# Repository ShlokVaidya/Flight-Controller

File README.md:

# Single Flight Controller (SFC) – Project Documentation

This repository contains the design files, schematic, and explanation for my custom Single Flight Controller (SFC). The goal of this project was to create a compact, modular, and fully functional flight controller with built-in sensors, logging capability, and support for standard RC aircraft peripherals. This design was heavily inspired by Hack Club’s Guided Project: SFC.

## Overview

This flight controller integrates all the essential modules required for basic autonomous flight experimentation on a single PCB. It includes computation, sensing, logging, and connectivity features normally spread across multiple boards.

The system is built around an STM32 microcontroller, with supporting components for power regulation, sensor interfacing, GPS reception, and servo control.

---

## Features

### 1. Microcontroller

The design centers around an STM32F722RETx MCU. It provides high-speed processing, multiple UART/SPI/I2C peripherals, and enough GPIO pins for sensors and servo output.

### 2. Four 3-Pin Servo Connectors

The board includes four standard 3-pin (Signal, 5V, GND) servo output connectors.
These can be used for:

* Control surfaces (aileron, elevator, rudder)
* Throttle signal
* Or any PWM-output peripheral

The PCB includes appropriate decoupling capacitors and routing to ensure clean, low-noise PWM signals.

### 3. UART Port

A dedicated UART port is broken out on the PCB.
This can be used for:

* Telemetry modules
* Debug serial output
* External communication
* RC Receiver (if using SBUS or another serial protocol)

### 4. Built-In Sensors and Modules

#### GPS Module: u-blox Neo-M9N

A high-performance GNSS receiver is integrated directly onto the PCB.
Features include:

* Fast acquisition
* High update rate options
* Reliable lock in outdoor flight conditions
* Direct UART communication with the STM32

#### Barometer

The barometer module (BMP-series) provides altitude estimation for stability and navigation algorithms.
It interfaces over I2C and includes proper filtering capacitors for noise reduction.

#### Accelerometer and Temperature Sensor

An onboard IMU provides acceleration data for movement detection and flight stabilization.
Temperature reading is also used internally by IMUs to compensate sensor drift.

### 5. SD Card Slot for Data Logging

The board includes a microSD card slot for logging flight data such as:

* GPS coordinates
* Barometric altitude
* Acceleration
* Temperature
* System debug information

The microcontroller communicates with the SD card via SPI.

### 6. Power Management

The design includes onboard regulators and filtering stages to provide stable supplies for:

* 5V rail (servos and peripherals)
* 3.3V rail (MCU, sensors, GPS)
* Noise isolation between digital and analog sections

---

## How the Flight Controller Was Designed

### Schematic Stage

I began by identifying the essential modules needed for the first version of the flight controller. I collected reference designs from datasheets and existing open-source boards, then arranged everything into a master schematic. Each module was divided into blocks:

* MCU core section
* Power regulation
* Servo outputs
* GPS
* Sensors (Barometer + IMU)
* SD card interface
* UART and additional connectors

I ensured all power, ground, and communication lines were properly labeled and referenced across schematic pages.

### PCB Routing

This was the most challenging part of the entire project.

#### Challenges Faced

1. **Dense routing around the STM32F7 MCU**
   The microcontroller has many high-speed pins in tight clusters. Routing SPI, I2C, UART, SWD, and PWM signals without crossing too many traces was difficult.

2. **Interference concerns between GPS and digital signals**
   GPS modules are sensitive to noise. Keeping the antenna section clean required careful placement and ground-plane management.

3. **Power distribution**
   Servos can draw significant current. Ensuring thick enough traces and minimizing voltage drops was a challenge.

4. **SD Card signal integrity**
   SPI lines need clean routing and matched lengths to avoid read/write instability. I had to reroute multiple times to avoid crosstalk.

5. **Fitting everything on a reasonable board size**
   With multiple connectors, sensors, and the MCU, arranging components efficiently took several iterations.

### What I Learned

1. **Importance of reference designs**
   Studying vendor schematics helped avoid basic mistakes, especially with decoupling and pull-up requirements.

2. **Routing strategy matters**
   Planning major traces (power rails, GPS lines, SD card lines) before others saves time.

3. **Decoupling capacitors are not optional**
   Correct placement greatly affected reliability during testing.

4. **Grounding techniques for mixed-signal boards**
   Separating analog and digital grounds and using ground pours improved noise performance.

5. **Iterative design is normal**
   The first layout is rarely perfect. Revision cycles teach you more than documentation ever will.

---

## Reference

This project was inspired by and based on concepts from Hack Club’s Guided Project: Single Flight Controller (SFC).

Their documentation, examples, and approach helped me understand:

* How to break complex designs into modular blocks
* Good PCB routing practices
* How sensing modules interact on a flight controller
* The importance of logging and debugging tools

---

## Conclusion

This Single Flight Controller is the result of combining research, reference designs, and hands-on PCB design practice. With integrated GPS, IMU, barometer, servo outputs, UART, and SD card logging on one board, it serves as a compact platform for experimenting with flight algorithms and embedded systems.

Note: 
Due to unavaiable components on JLCPCB i would request to get tickets instead of the PCB.

Thank You,
Shlok Vaidya

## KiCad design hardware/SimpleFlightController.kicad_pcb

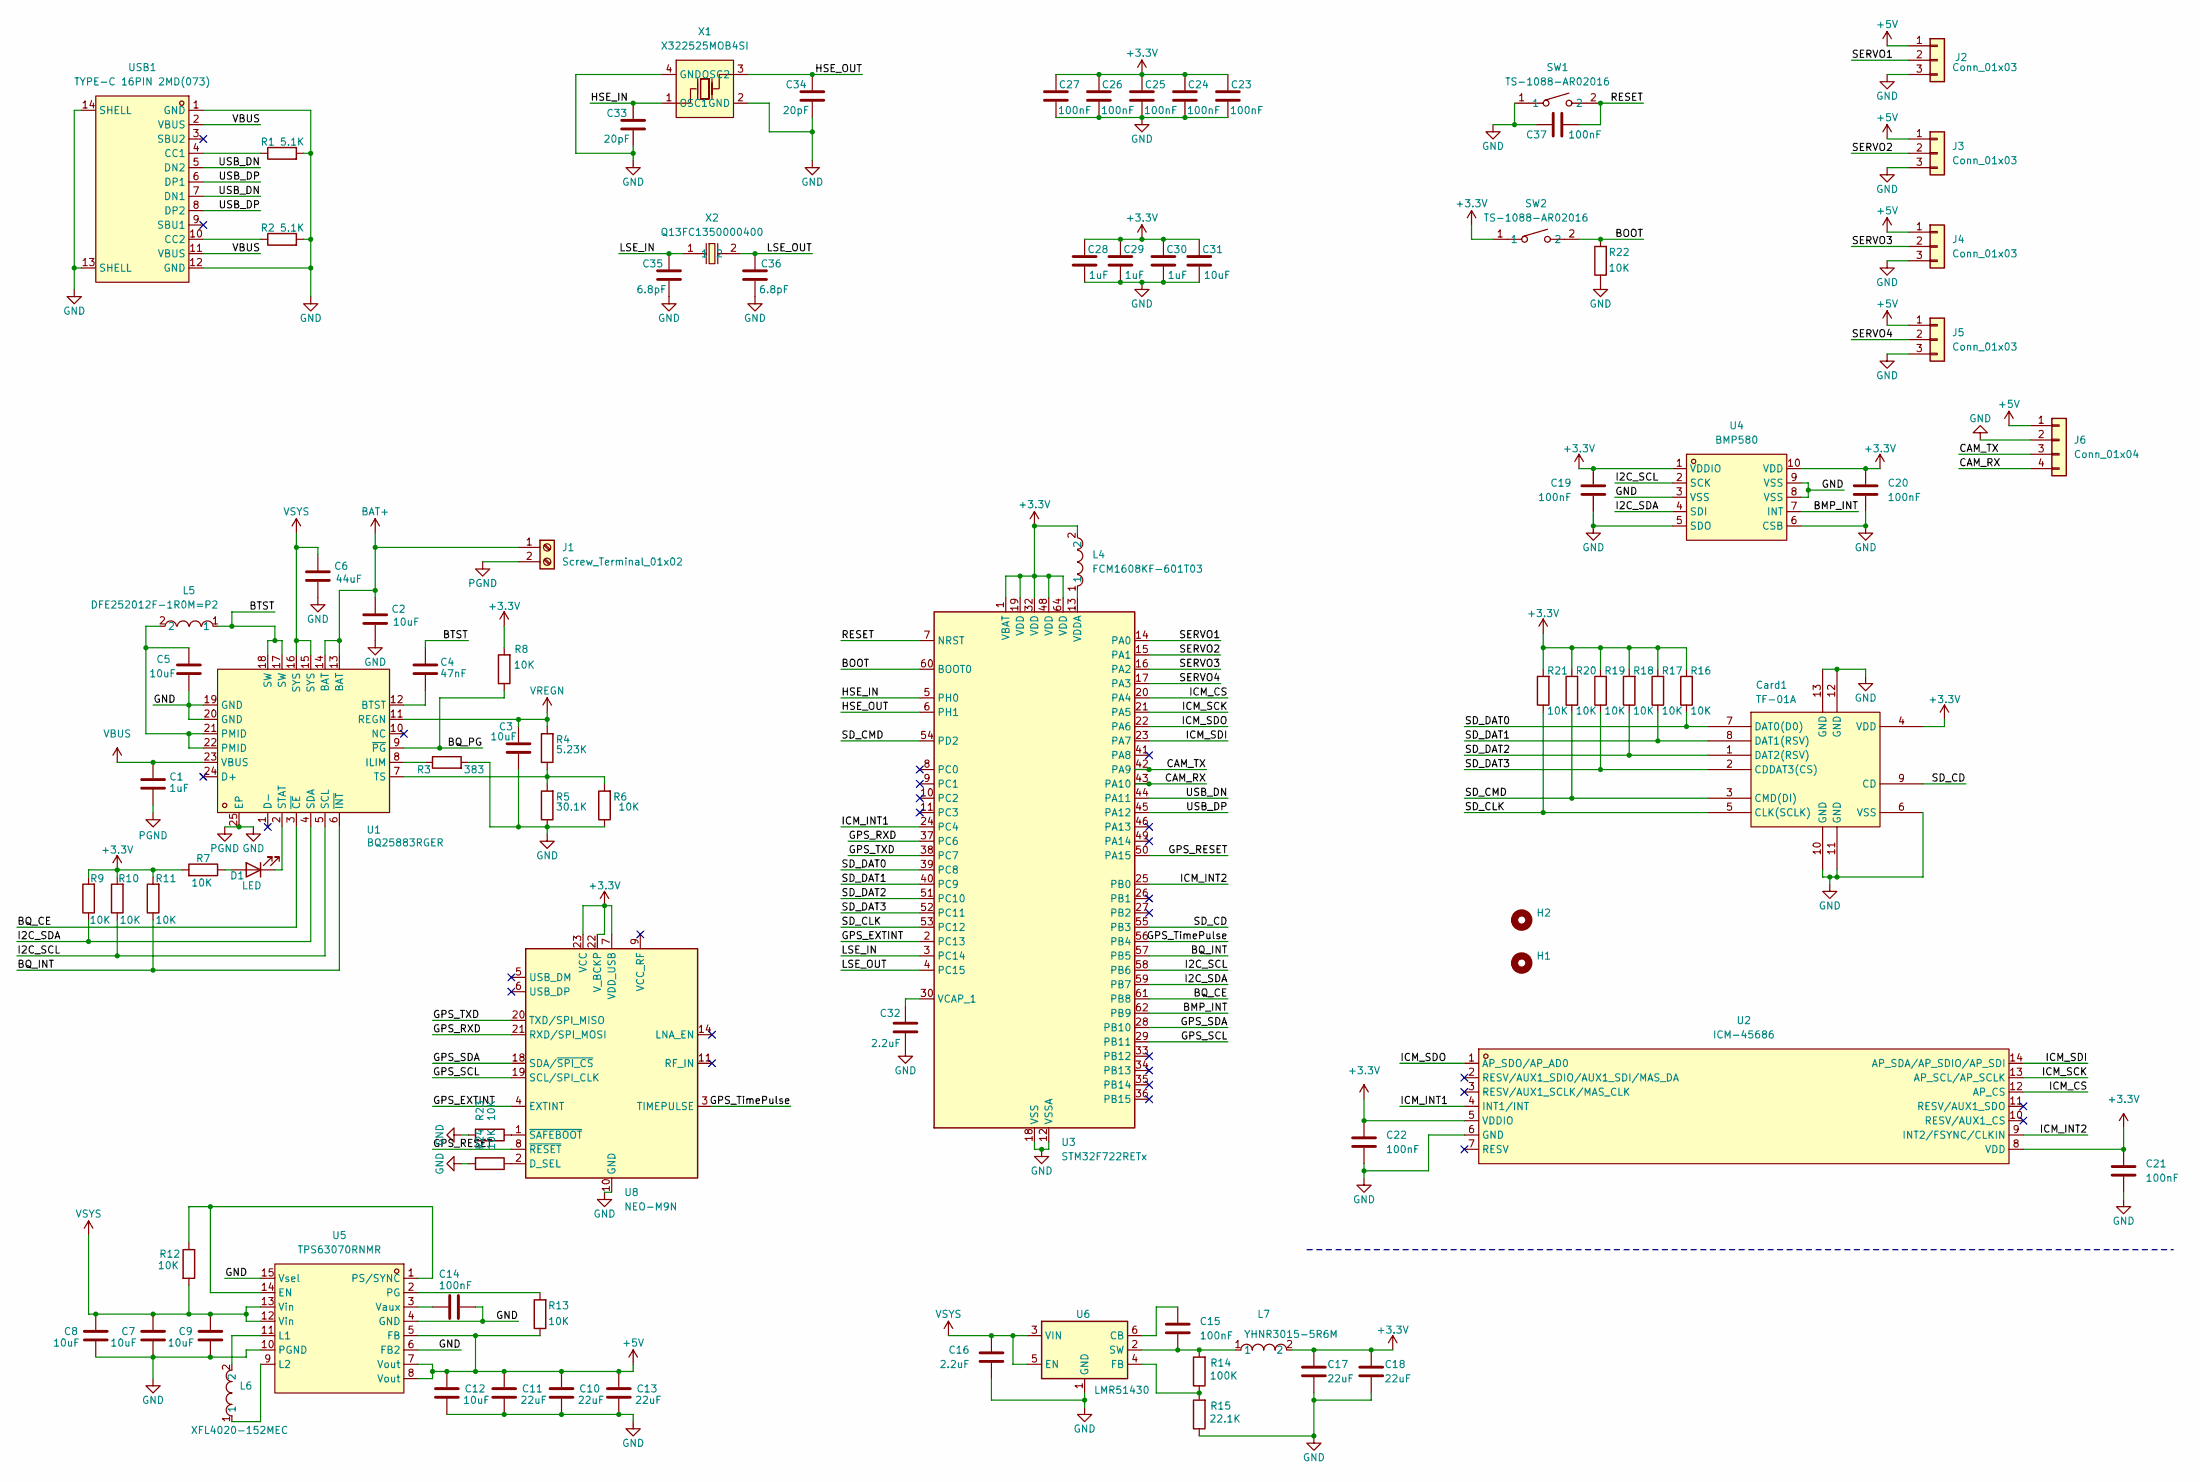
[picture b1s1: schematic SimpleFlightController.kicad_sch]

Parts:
C1, C28, C29, C30: 1uF; C_0402_1005Metric
C2, C9, C12: 10uF; C_0603_1608Metric
C3, C5, C31: 10uF; C_0402_1005Metric
C4: 47nF; C_0201_0603Metric
C6: 44uF; C_0603_1608Metric
C7, C8: 10uF; C_0805_2012Metric
C10, C11, C13: 22uF; C_0805_2012Metric
C14, C15, C19, C20, C21, C22, C23, C24, C25, C26, C27, C37: 100nF; C_0201_0603Metric
C16: 2.2uF; C_0603_1608Metric
C17, C18: 22uF; C_0402_1005Metric
C32: 2.2uF; C_0201_0603Metric
C33, C34: 20pF; C_0201_0603Metric
C35, C36: 6.8pF; C_0201_0603Metric
Card1: TF-01A; TF-SMD_TF-01A; LCSC Part C91145
D1: LED; LED_0402_1005Metric
H1, H2: MountingHole; MountingHole_2.2mm_M2
J1: Screw_Terminal_01x02; TerminalBlock_Xinya_XY308-2.54-2P_1x02_P2.54mm_Horizontal
J2, J3, J4, J5: Conn_01x03; PinHeader_1x03_P2.54mm_Vertical
J6: Conn_01x04; PinHeader_1x04_P2.54mm_Vertical
L4: FCM1608KF-601T03; L0603; LCSC Part C141723
L5: DFE252012F-1R0M=P2; L2520; LCSC Part C435392
L6: XFL4020-152MEC; IND-SMD_L4.0-W4.0-A; LCSC Part C3033018
L7: YHNR3015-5R6M; IND-SMD_L3.0-W3.0; LCSC Part C18236327
R1, R2: 5.1K; R_0201_0603Metric
R3: 383; R_0201_0603Metric
R4: 5.23K; R_0201_0603Metric
R5: 30.1K; R_0201_0603Metric
R6, R7, R8, R9, R10, R11, R12, R13, R16, R17, R18, R19, R20, R21, R22, R23, R24: 10K; R_0201_0603Metric
R14: 100K; R_0402_1005Metric
R15: 22.1K; R_0402_1005Metric
SW1, SW2: TS-1088-AR02016; SW-SMD_L3.9-W3.0-P4.45; LCSC Part C720477
U1: BQ25883RGER; VFQFPN-24_L4.0-W4.0-P0.50-BL-EP2.8; LCSC Part C544362
U2: ICM-45686; LGA-14_L3.0-W2.5-P0.50-TL; LCSC Part C22459454
U3: STM32F722RETx; LQFP-64_10x10mm_P0.5mm
U4: BMP580; LGA-10_L2.0-W2.0-P0.50-TL_BMP580; LCSC Part C22391138
U5: TPS63070RNMR; VQFN-HR-15_L3.0-W2.5-P0.50-BL_TPS63070RNMR; LCSC Part C109322
U6: LMR51430; SOT-23-6
U8: NEO-M9N; ublox_NEO
USB1: TYPE-C 16PIN 2MD(073); USB-C-SMD_TYPE-C-6PIN-2MD-073; LCSC Part C2765186
X1: X322525MOB4SI; CRYSTAL-SMD_4P-L3.2-W2.5-BL; LCSC Part C9006
X2: Q13FC1350000400; FC-135R_L3.2-W1.5; LCSC Part C32346

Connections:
+3.3V: C17.1, C18.1, C19.1, C20.1, C21.1, C22.1, C23.1, C24.1, C25.1, C26.1, C27.1, C28.1, C29.1, C30.1, C31.1, Card1.4 (VDD), L4.2, L7.2, R7.2, R8.2, R9.2, R10.2, R11.2, R16.2, R17.2, R18.2, R19.2, R20.2, R21.2, SW2.1, U2.5 (VDDIO), U2.8 (VDD), U3.1 (VBAT), U3.19 (VDD), U3.32 (VDD), U3.48 (VDD), U3.64 (VDD), U4.1 (VDDIO), U4.10 (VDD), U8.7 (VDD_USB), U8.22 (V_BCKP), U8.23 (VCC)
+5V: C10.1, C11.1, C12.1, C13.1, J2.1, J3.1, J4.1, J5.1, J6.1, R13.1, U5.5 (FB), U5.7 (Vout), U5.8 (Vout)
/BMP_INT: U3.62 (PB9), U4.7 (INT)
/BOOT: R22.2, SW2.2, U3.60 (BOOT0)
/BQ_CE: U1.3 (~CE), U3.61 (PB8)
/BQ_INT: R11.1, U1.6 (~INT), U3.57 (PB5)
/BQ_PG: R8.1, U1.9 (~PG)
/BTST: C4.1, L5.1, U1.17 (SW), U1.18 (SW)
/CAM_RX: J6.4, U3.43 (PA10)
/CAM_TX: J6.3, U3.42 (PA9)
/GPS_EXTINT: U3.2 (PC13), U8.4 (EXTINT)
/GPS_RESET: U3.50 (PA15), U8.8 (~RESET)
/GPS_RXD: U3.37 (PC6), U8.21 (RXD/SPI_MOSI)
/GPS_SCL: U3.29 (PB11), U8.19 (SCL/SPI_CLK)
/GPS_SDA: U3.28 (PB10), U8.18 (SDA/~SPI_CS)
/GPS_TXD: U3.38 (PC7), U8.20 (TXD/SPI_MISO)
/GPS_TimePulse: U3.56 (PB4), U8.3 (TIMEPULSE)
/HSE_IN: C33.1, U3.5 (PH0), X1.1 (OSC1)
/HSE_OUT: C34.1, U3.6 (PH1), X1.3 (OSC2)
/I2C_SCL: R10.1, U1.5 (SCL), U3.58 (PB6), U4.2 (SCK)
/I2C_SDA: R9.1, U1.4 (SDA), U3.59 (PB7), U4.4 (SDI)
/ICM_CS: U2.12 (AP_CS), U3.20 (PA4)
/ICM_INT1: U2.4 (INT1/INT), U3.24 (PC4)
/ICM_INT2: U2.9 (INT2/FSYNC/CLKIN), U3.25 (PB0)
/ICM_SCK: U2.13 (AP_SCL/AP_SCLK), U3.21 (PA5)
/ICM_SDI: U2.14 (AP_SDA/AP_SDIO/AP_SDI), U3.23 (PA7)
/ICM_SDO: U2.1 (AP_SDO/AP_AD0), U3.22 (PA6)
/LSE_IN: C35.1, U3.3 (PC14), X2.1
/LSE_OUT: C36.1, U3.4 (PC15), X2.2
/RESET: C37.2, SW1.2, U3.7 (NRST)
/SD_CD: Card1.9 (CD), U3.55 (PB3)
/SD_CLK: Card1.5 (CLK(SCLK)), R21.1, U3.53 (PC12)
/SD_CMD: Card1.3 (CMD(DI)), R20.1, U3.54 (PD2)
/SD_DAT0: Card1.7 (DAT0(D0)), R16.1, U3.39 (PC8)
/SD_DAT1: Card1.8 (DAT1(RSV)), R17.1, U3.40 (PC9)
/SD_DAT2: Card1.1 (DAT2(RSV)), R18.1, U3.51 (PC10)
/SD_DAT3: Card1.2 (CDDAT3(CS)), R19.1, U3.52 (PC11)
/SERVO1: J2.2, U3.14 (PA0)
/SERVO2: J3.2, U3.15 (PA1)
/SERVO3: J4.2, U3.16 (PA2)
/SERVO4: J5.2, U3.17 (PA3)
/USB_DN: U3.44 (PA11), USB1.5 (DN2), USB1.7 (DN1)
/USB_DP: U3.45 (PA12), USB1.6 (DP1), USB1.8 (DP2)
BAT+: C2.1, J1.1, U1.13 (BAT), U1.14 (BAT)
GND: C1.2, C2.2, C3.2, C5.2, C6.2, C7.2, C8.2, C9.2, C10.2, C11.2, C12.2, C13.2, C14.2, C16.2, C17.2, C18.2, C19.2, C20.2, C21.2, C22.2, C23.2, C24.2, C25.2, C26.2, C27.2, C28.2, C29.2, C30.2, C31.2, C32.2, C33.2, C34.2, C35.2, C36.2, C37.1, Card1.6 (VSS), Card1.10 (GND), Card1.11 (GND), Card1.12 (GND), Card1.13 (GND), J1.2, J2.3, J3.3, J4.3, J5.3, J6.2, R1.2, R2.2, R3.2, R5.1, R6.1, R15.1, R22.1, R23.2, R24.2, SW1.1, U1.19 (GND), U1.20 (GND), U1.25 (EP), U2.6 (GND), U3.12 (VSSA), U3.18 (VSS), U3.31 (VSS), U3.47 (VSS), U3.63 (VSS), U4.3 (VSS), U4.5 (SDO), U4.6 (CSB), U4.8 (VSS), U4.9 (VSS), U5.4 (GND), U5.6 (FB2), U5.10 (PGND), U5.15 (Vsel), U6.1 (GND), U8.10 (GND), U8.12 (GND), U8.13 (GND), U8.24 (GND), USB1.1 (GND), USB1.12 (GND), USB1.13 (SHELL), USB1.14 (SHELL), X1.2 (GND), X1.4 (GND)
unnamed: C5.1, L5.2, U1.21 (PMID), U1.22 (PMID)
unnamed: D1.2 (A), R7.1
unnamed: D1.1 (K), U1.2 (STAT)
unnamed: C4.2, U1.12 (BTST)
unnamed: R3.1, U1.8 (ILIM)
unnamed: R4.1, R5.2, R6.2, U1.7 (TS)
unnamed: C32.1, U3.30 (VCAP_1)
unnamed: L4.1, U3.13 (VDDA)
unnamed: R12.1, U5.1 (PS/SYNC), U5.14 (EN)
unnamed: L6.2, U5.11 (L1)
unnamed: L6.1, U5.9 (L2)
unnamed: R13.2, U5.2 (PG)
unnamed: C14.1, U5.3 (Vaux)
unnamed: C15.1, U6.6 (CB)
unnamed: R14.1, R15.2, U6.4 (FB)
unnamed: C15.2, L7.1, R14.2, U6.2 (SW)
unnamed: R24.1, U8.2 (D_SEL)
unnamed: R23.1, U8.1 (~SAFEBOOT)
unnamed: R1.1, USB1.4 (CC1)
unnamed: R2.1, USB1.10 (CC2)
VBUS: C1.1, U1.23 (VBUS), USB1.2 (VBUS), USB1.11 (VBUS)
VREGN: C3.1, R4.2, U1.11 (REGN)
VSYS: C6.1, C7.1, C8.1, C9.1, C16.1, R12.2, U1.15 (SYS), U1.16 (SYS), U5.12 (Vin), U5.13 (Vin), U6.3 (VIN), U6.5 (EN)

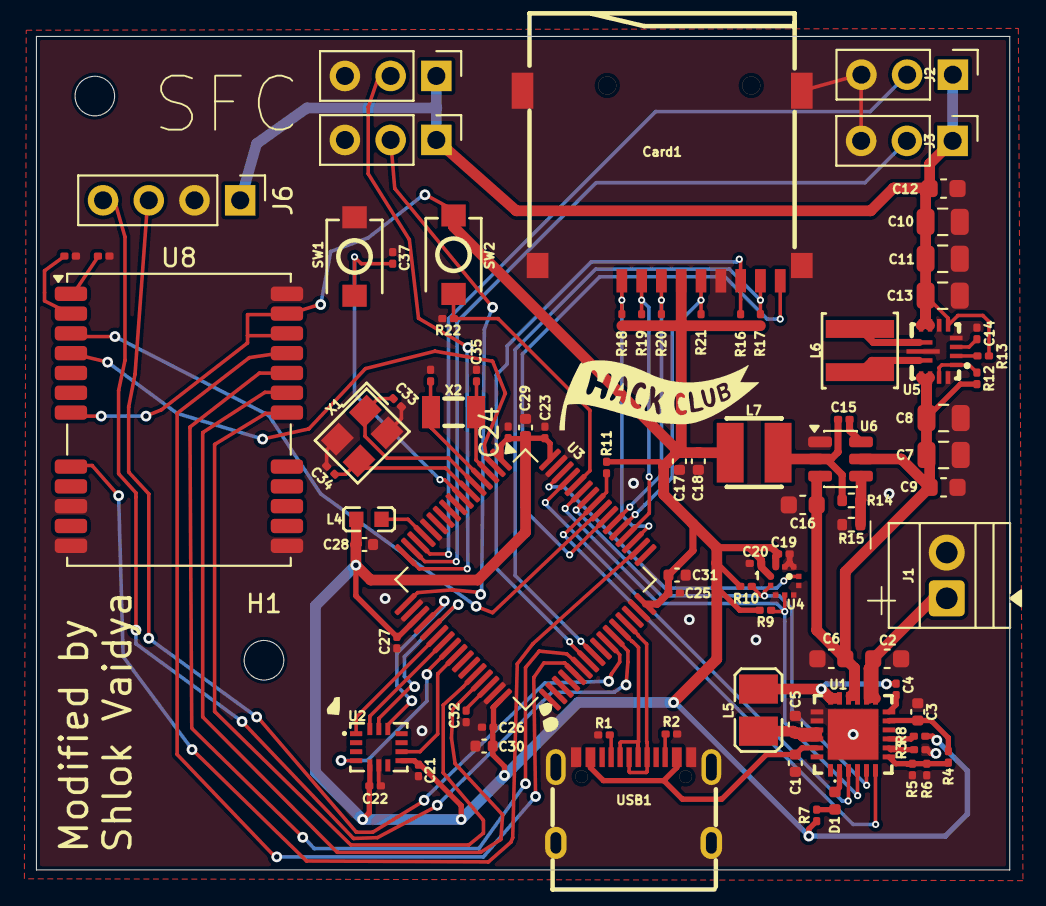
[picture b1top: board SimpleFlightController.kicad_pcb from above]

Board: 2 copper layers, 54.1 x 46.3 mm, 87 parts (0 on the bottom side), 68 nets.

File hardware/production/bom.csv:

Designator,Footprint,Quantity,Value,LCSC Part #
"C1, C28, C29, C30",0402,4,1uF,
"C10, C11, C13",0805,3,22uF,
"C12, C2, C9",0603,3,10uF,
"C14, C15, C19, C20, C21, C22, C23, C24, C25, C26, C27, C37",0201,12,100nF,
C16,0603,1,2.2uF,
"C17, C18",0402,2,22uF,
"C3, C31, C5",0402,3,10uF,
C32,0201,1,2.2uF,
"C33, C34",0201,2,20pF,
"C35, C36",0201,2,6.8pF,
C4,0201,1,47nF,
C6,0603,1,44uF,
"C7, C8",0805,2,10uF,
CARD1,TF-SMD_TF-01A,1,TF-01A,C91145
D1,0402,1,LED,
J1,TerminalBlock_Xinya_XY308-2.54-2P_1x02_P2.54mm_Horizontal,1,Screw_Terminal_01x02,
"J2, J3, J4, J5",PinHeader_1x03_P2.54mm_Vertical,4,Conn_01x03,
L4,L0603,1,FCM1608KF-601T03,C141723
L5,L2520,1,DFE252012F-1R0M=P2,C435392
L6,IND-SMD_L4.0-W4.0-A,1,XFL4020-152MEC,C3033018
L7,IND-SMD_L3.0-W3.0,1,YHNR3015-5R6M,C18236327
"R1, R2",0201,2,5.1K,
"R10, R11, R12, R13, R16, R17, R18, R19, R20, R21, R22, R23, R24, R6, R7, R8, R9",0201,17,10K,
R14,0402,1,100K,
R15,0402,1,22.1K,
R3,0201,1,383,
R4,0201,1,5.23K,
R5,0201,1,30.1K,
"SW1, SW2",SW-SMD_L3.9-W3.0-P4.45,2,TS-1088-AR02016,C720477
U1,VFQFPN-24_L4.0-W4.0-P0.50-BL-EP2.8,1,BQ25883RGER,C544362
U2,LGA-14_L3.0-W2.5-P0.50-TL,1,ICM-45686,C22459454
U3,LQFP-64_10x10mm_P0.5mm,1,STM32F722RETx,
U4,LGA-10_L2.0-W2.0-P0.50-TL_BMP580,1,BMP580,C22391138
U5,VQFN-HR-15_L3.0-W2.5-P0.50-BL_TPS63070RNMR,1,TPS63070RNMR,C109322
U6,SOT-23-6,1,LMR51430,
U8,ublox_NEO,1,NEO-M9N,
USB1,USB-C-SMD_TYPE-C-6PIN-2MD-073,1,TYPE-C 16PIN 2MD(073),C2765186
X1,CRYSTAL-SMD_4P-L3.2-W2.5-BL,1,X322525MOB4SI,C9006
X2,FC-135R_L3.2-W1.5,1,Q13FC1350000400,C32346

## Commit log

2025-11-28 SFC v1.2
2025-11-30 SFC v2
